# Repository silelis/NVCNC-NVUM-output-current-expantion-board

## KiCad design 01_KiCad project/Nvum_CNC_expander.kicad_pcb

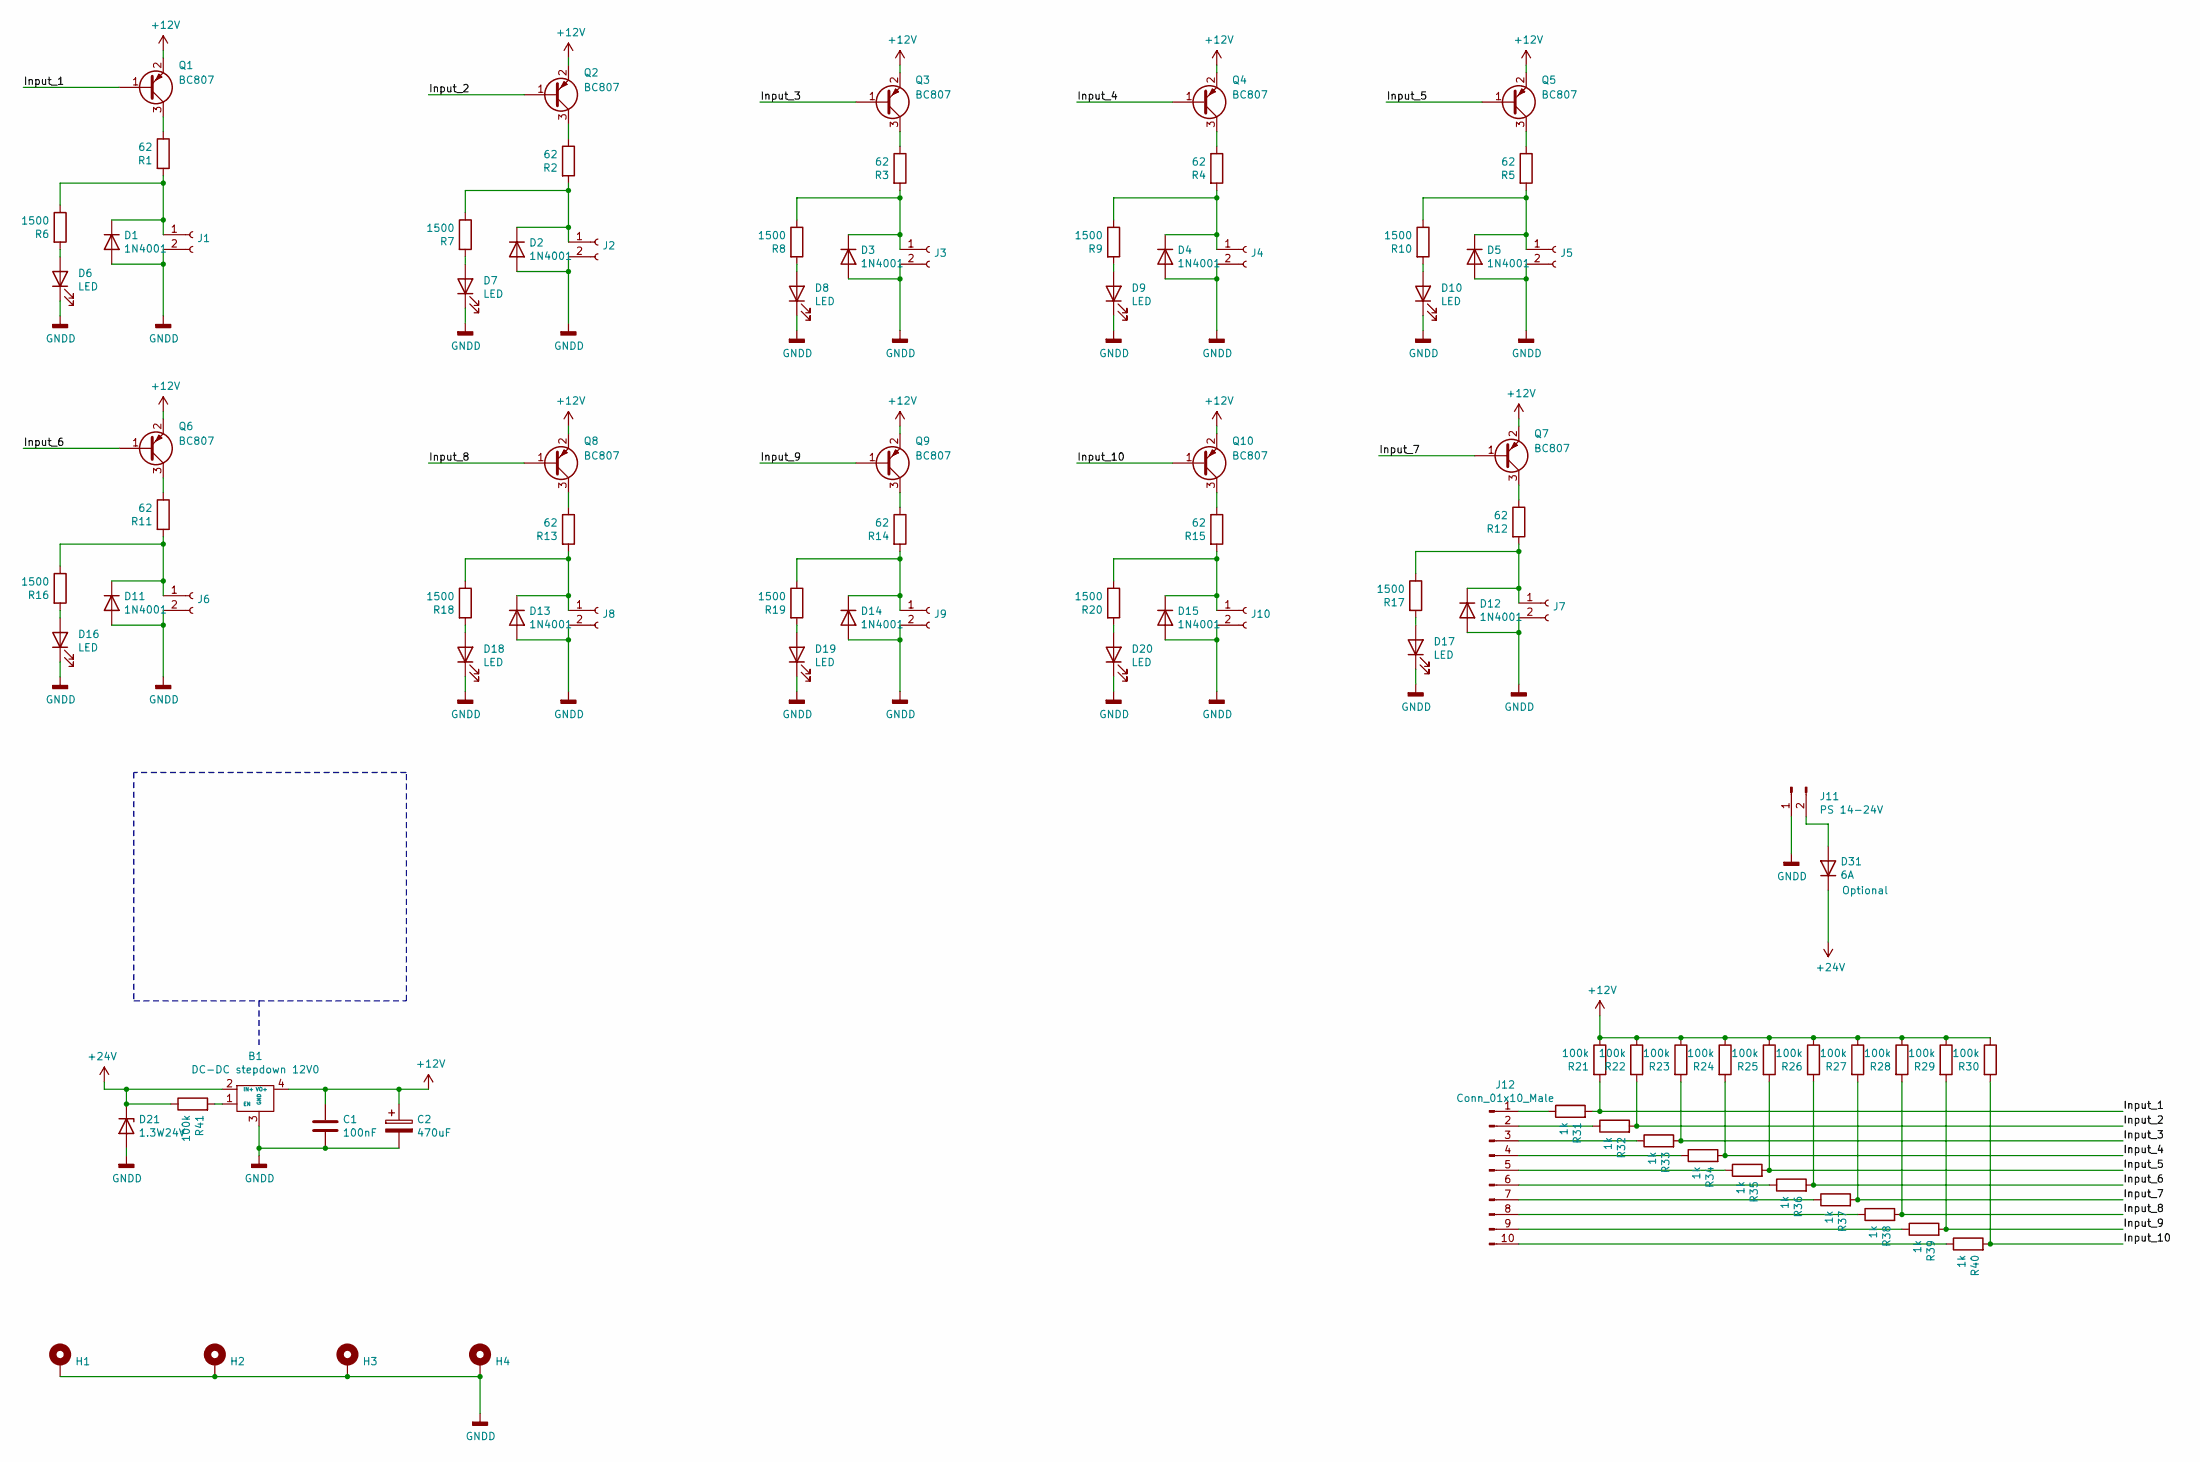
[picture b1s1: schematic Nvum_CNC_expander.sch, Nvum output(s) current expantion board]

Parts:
B1: DC-DC stepdown 12V0; DC-DC_24V_Stepdown_brekout_horizontal
C1: 100nF; C_0805_2012Metric_Pad1.18x1.45mm_HandSolder
C2: 470uF; CP_Radial_Tantal_D8.0mm_P5.00mm
D1, D2, D3, D4, D5, D11, D12, D13, D14, D15: 1N4001; D_DO-41_SOD81_P10.16mm_Horizontal
D6, D7, D8, D9, D10, D16, D17, D18, D19, D20: LED; LED_D3.0mm
D21: 1.3W24V; D_A-405_P12.70mm_Horizontal
D31: 6A; D_5KP_P12.70mm_Horizontal
H1, H2, H3, H4: MountingHole_Pad; MountingHole_3.2mm_M3_DIN965_Pad
J1, J2, J3, J4, J5, J6, J7, J8, J9, J10: Conn_01x02_Female; PhoenixContact_MCV_1,5_2-G-3.81_1x02_P3.81mm_Vertical
J11: PS 14-24V; PhoenixContact_MCV_1,5_2-G-3.81_1x02_P3.81mm_Vertical
J12: Conn_01x10_Male; PhoenixContact_MC_1,5_10-GF-3.81_1x10_P3.81mm_Horizontal_Th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
Q1, Q2, Q3, Q4, Q5, Q6, Q7, Q8, Q9, Q10: BC807; SOT-23; JLCPBC C107301
R1, R2, R3, R4, R5, R11, R12, R13, R14, R15: 62; R_Axial_DIN0207_L6.3mm_D2.5mm_P2.54mm_Vertical
R6, R7, R8, R9, R10, R16, R17, R18, R19, R20: 1500; R_0805_2012Metric_Pad1.20x1.40mm_HandSolder
R21, R22, R23, R24, R25, R26, R27, R28, R29, R30, R41: 100k; R_0805_2012Metric_Pad1.20x1.40mm_HandSolder
R31, R32, R33, R34, R35, R36, R37, R38, R39, R40: 1k; R_0805_2012Metric_Pad1.20x1.40mm_HandSolder

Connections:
+12V: B1.4 (VO+), C1.1, C2.1, Q1.2 (E), Q2.2 (E), Q3.2 (E), Q4.2 (E), Q5.2 (E), Q6.2 (E), Q7.2 (E), Q8.2 (E), Q9.2 (E), Q10.2 (E), R21.1, R22.1, R23.1, R24.1, R25.1, R26.1, R27.1, R28.1, R29.1, R30.1
+24V: B1.2 (IN+), D21.1 (K), D31.2 (K), R41.1
/Input_1: Q1.1 (B), R21.2, R31.2
/Input_2: Q2.1 (B), R22.2, R32.2
/Input_3: Q3.1 (B), R23.2, R33.2
/Input_4: Q4.1 (B), R24.2, R34.2
/Input_5: Q5.1 (B), R25.2, R35.2
/Input_6: Q6.1 (B), R26.2, R36.2
/Input_7: Q7.1 (B), R27.2, R37.2
/Input_8: Q8.1 (B), R28.2, R38.2
/Input_9: Q9.1 (B), R29.2, R39.2
/Input_10: Q10.1 (B), R30.2, R40.2
GNDD: B1.3 (GND), C1.2, C2.2, D1.2 (A), D2.2 (A), D3.2 (A), D4.2 (A), D5.2 (A), D6.1 (K), D7.1 (K), D8.1 (K), D9.1 (K), D10.1 (K), D11.2 (A), D12.2 (A), D13.2 (A), D14.2 (A), D15.2 (A), D16.1 (K), D17.1 (K), D18.1 (K), D19.1 (K), D20.1 (K), D21.2 (A), H1.1, H2.1, H3.1, H4.1, J1.2, J2.2, J3.2, J4.2, J5.2, J6.2, J7.2, J8.2, J9.2, J10.2, J11.1
unnamed: B1.1 (EN), R41.2
unnamed: D1.1 (K), J1.1, R1.2, R6.1
unnamed: D2.1 (K), J2.1, R2.2, R7.1
unnamed: D3.1 (K), J3.1, R3.2, R8.1
unnamed: D4.1 (K), J4.1, R4.2, R9.1
unnamed: D5.1 (K), J5.1, R5.2, R10.1
unnamed: D6.2 (A), R6.2
unnamed: D7.2 (A), R7.2
unnamed: D8.2 (A), R8.2
unnamed: D9.2 (A), R9.2
unnamed: D10.2 (A), R10.2
unnamed: D11.1 (K), J6.1, R11.2, R16.1
unnamed: D12.1 (K), J7.1, R12.2, R17.1
unnamed: D13.1 (K), J8.1, R13.2, R18.1
unnamed: D14.1 (K), J9.1, R14.2, R19.1
unnamed: D15.1 (K), J10.1, R15.2, R20.1
unnamed: D16.2 (A), R16.2
unnamed: D17.2 (A), R17.2
unnamed: D18.2 (A), R18.2
unnamed: D19.2 (A), R19.2
unnamed: D20.2 (A), R20.2
unnamed: D31.1 (A), J11.2
unnamed: J12.1, R31.1
unnamed: J12.2, R32.1
unnamed: J12.3, R33.1
unnamed: J12.4, R34.1
unnamed: J12.5, R35.1
unnamed: J12.6, R36.1
unnamed: J12.7, R37.1
unnamed: J12.8, R38.1
unnamed: J12.9, R39.1
unnamed: J12.10, R40.1
unnamed: Q1.3 (C), R1.1
unnamed: Q2.3 (C), R2.1
unnamed: Q3.3 (C), R3.1
unnamed: Q4.3 (C), R4.1
unnamed: Q5.3 (C), R5.1
unnamed: Q6.3 (C), R11.1
unnamed: Q7.3 (C), R12.1
unnamed: Q8.3 (C), R13.1
unnamed: Q9.3 (C), R14.1
unnamed: Q10.3 (C), R15.1

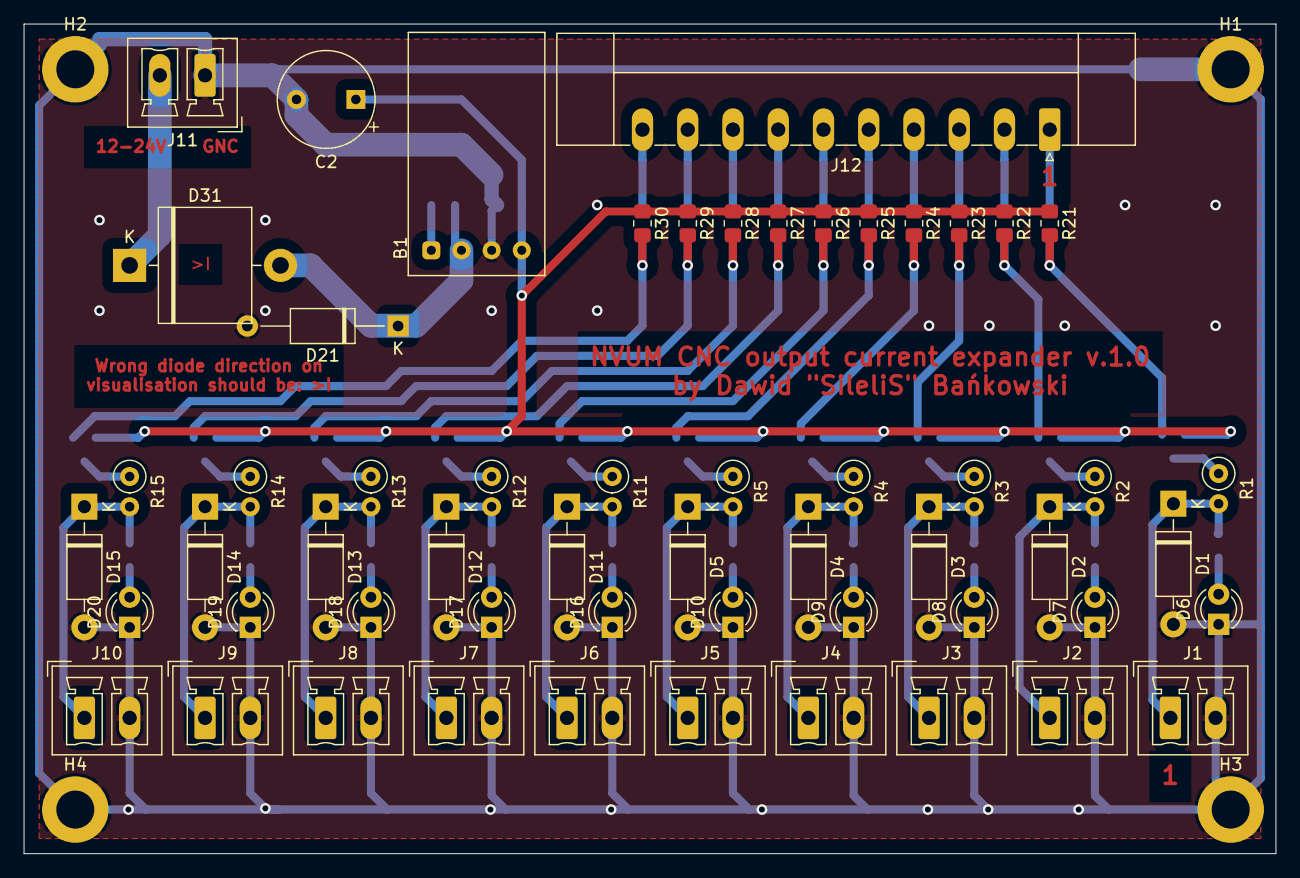
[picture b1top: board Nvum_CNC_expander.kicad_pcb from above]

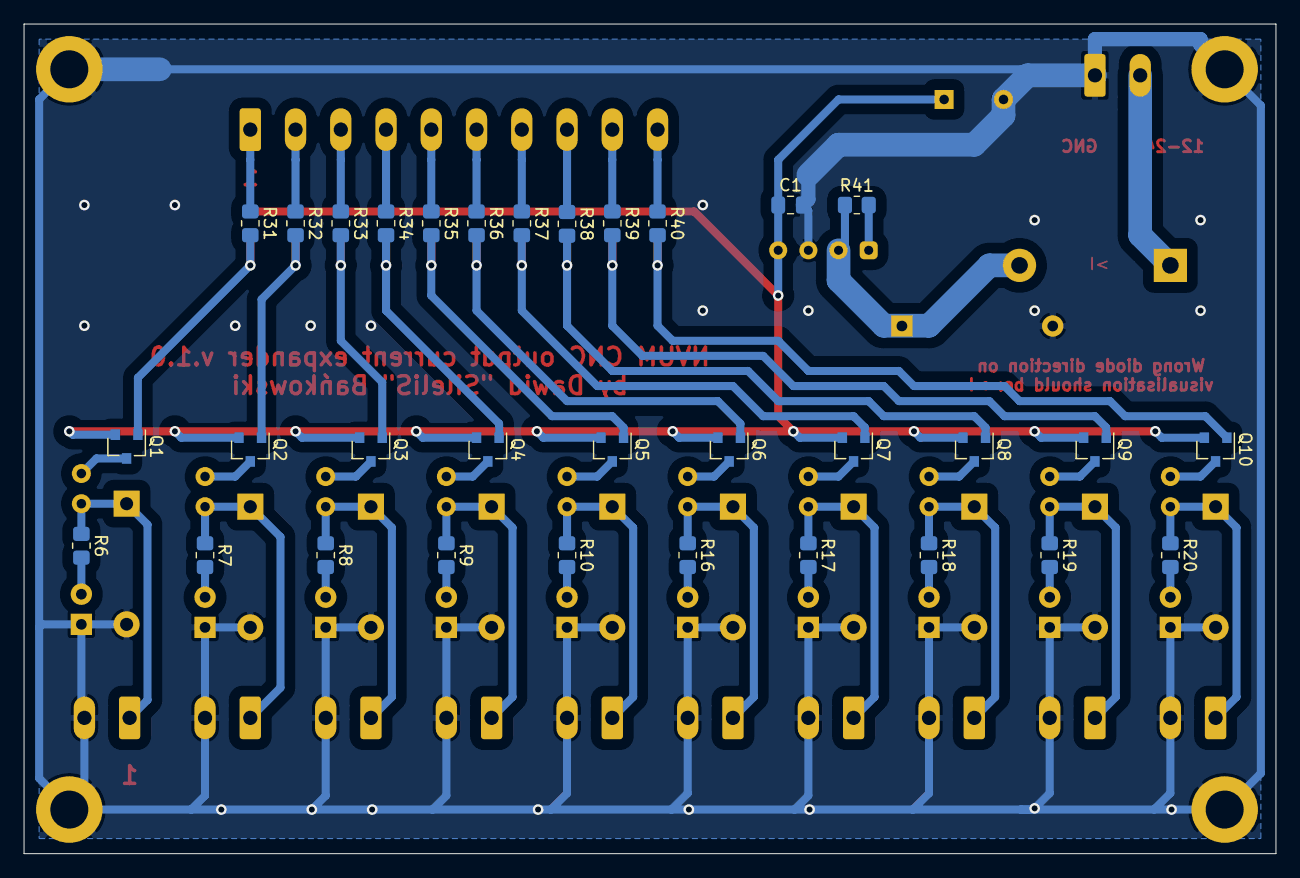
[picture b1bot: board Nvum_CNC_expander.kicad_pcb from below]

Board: 2 copper layers, 105.4 x 69.8 mm, 92 parts (32 on the bottom side), 55 nets.
